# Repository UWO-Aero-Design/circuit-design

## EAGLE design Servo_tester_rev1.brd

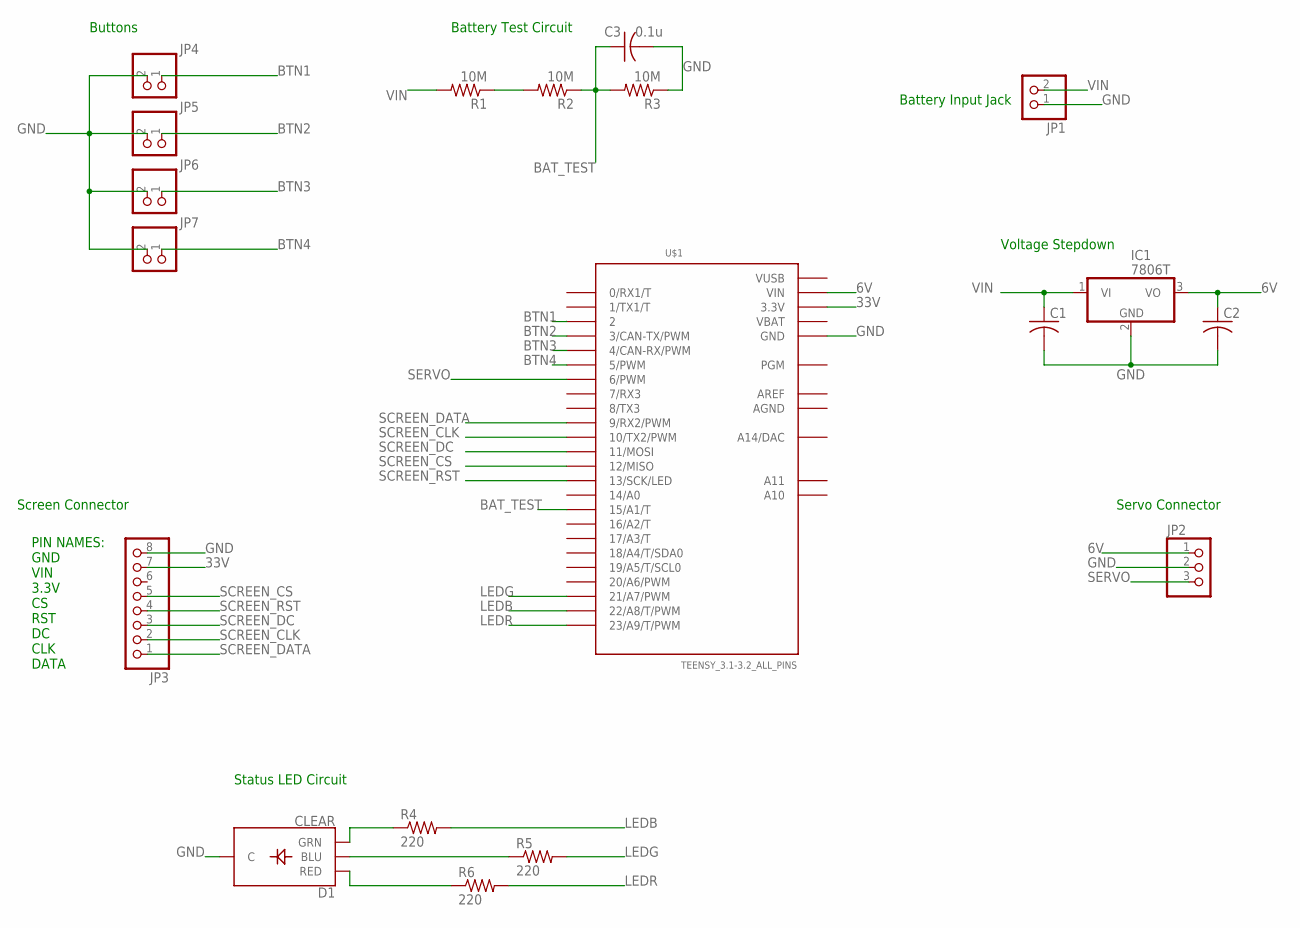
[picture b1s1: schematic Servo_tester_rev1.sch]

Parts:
C1, C2: C-US050-024X044; C050-024X044
C3: 0.1u; C050-024X044
D1: CLEAR; LED-RGB-THRU
IC1: 7806T; TO220H
JP1, JP4, JP5, JP6, JP7: HEADER-1X2ROUND; 1X02_ROUND
JP2: HEADER-1X3ROUND; 1X03_ROUND
JP3: HEADER-1X870MIL; 1X08_ROUND_70
R1, R2, R3: 10M; 0204/5
R4, R5, R6: 220; 0204/5
U$1: TEENSY_3.1-3.2_ALL_PINS; TEENSY_3.0-3.2&LC_ALL_PINS

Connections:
6V: C2.1, IC1.3 (VO), JP2.1, U$1.VIN
33V: JP3.7, U$1.3.3V, U$1.3.3V1 (3.3V)
AGND: U$1.AGND
AREF: U$1.AREF
BAT_TEST: C3.1, R2.1, R3.2, U$1.15/A1 (15/A1/T)
BTN1: JP4.1, U$1.2
BTN2: JP5.1, U$1.3 (3/CAN-TX/PWM)
BTN3: JP6.1, U$1.4 (4/CAN-RX/PWM)
BTN4: JP7.1, U$1.5 (5/PWM)
GND: C1.2, C2.2, C3.2, D1.2 (C), IC1.2 (GND), JP1.1, JP2.2, JP3.8, JP4.2, JP5.2, JP6.2, JP7.2, R3.1, U$1.GND, U$1.GND1 (GND)
LEDB: R4.2, U$1.22/A8 (22/A8/T/PWM)
LEDG: R5.2, U$1.21/A7 (21/A7/PWM)
LEDR: R6.2, U$1.23/A9 (23/A9/T/PWM)
unnamed: D1.1 (RED), R6.1
unnamed: D1.3 (GRN), R4.1
unnamed: D1.4 (BLU), R5.1
unnamed: R1.1, R2.2
SCREEN_CLK: JP3.2, U$1.10 (10/TX2/PWM)
SCREEN_CS: JP3.5, U$1.12 (12/MISO)
SCREEN_DATA: JP3.1, U$1.9 (9/RX2/PWM)
SCREEN_DC: JP3.3, U$1.11 (11/MOSI)
SCREEN_RST: JP3.4, U$1.13 (13/SCK/LED)
SERVO: JP2.3, U$1.6 (6/PWM)
VIN: C1.1, IC1.1 (VI), JP1.2, R1.2, U$1.VBAT
VUSB: U$1.VUSB

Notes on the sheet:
PIN NAMES: GND VIN 3.3V CS RST DC CLK DATA
Battery Input Jack
Battery Test Circuit
Voltage Stepdown
Servo Connector
Status LED Circuit
Screen Connector
Buttons

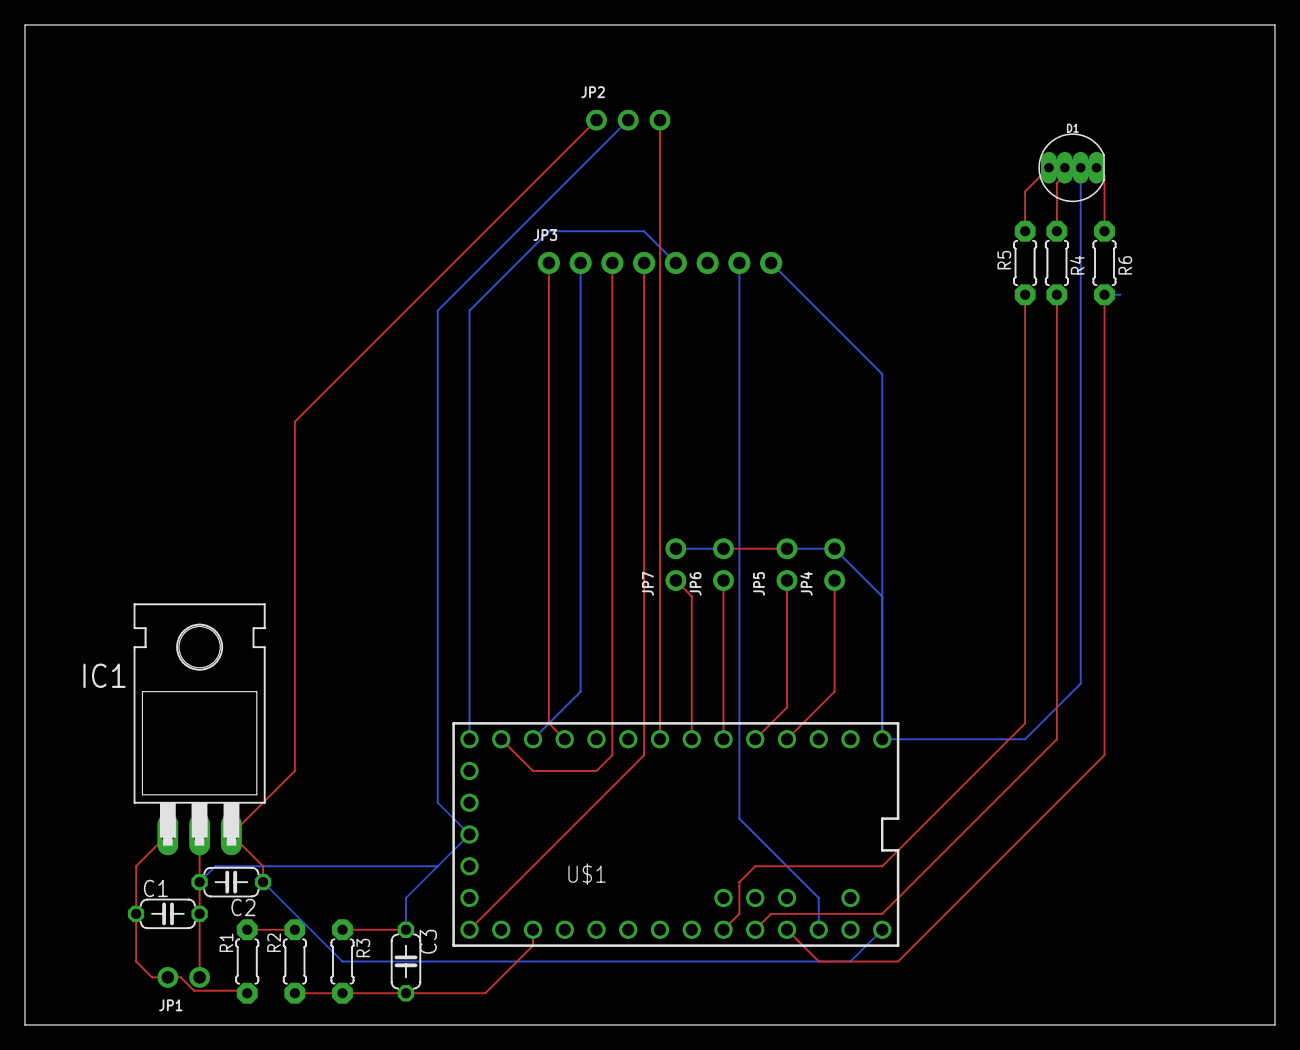
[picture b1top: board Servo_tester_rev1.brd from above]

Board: 2 copper layers, 100.0 x 80.0 mm, 19 parts (0 on the bottom side), 22 nets.

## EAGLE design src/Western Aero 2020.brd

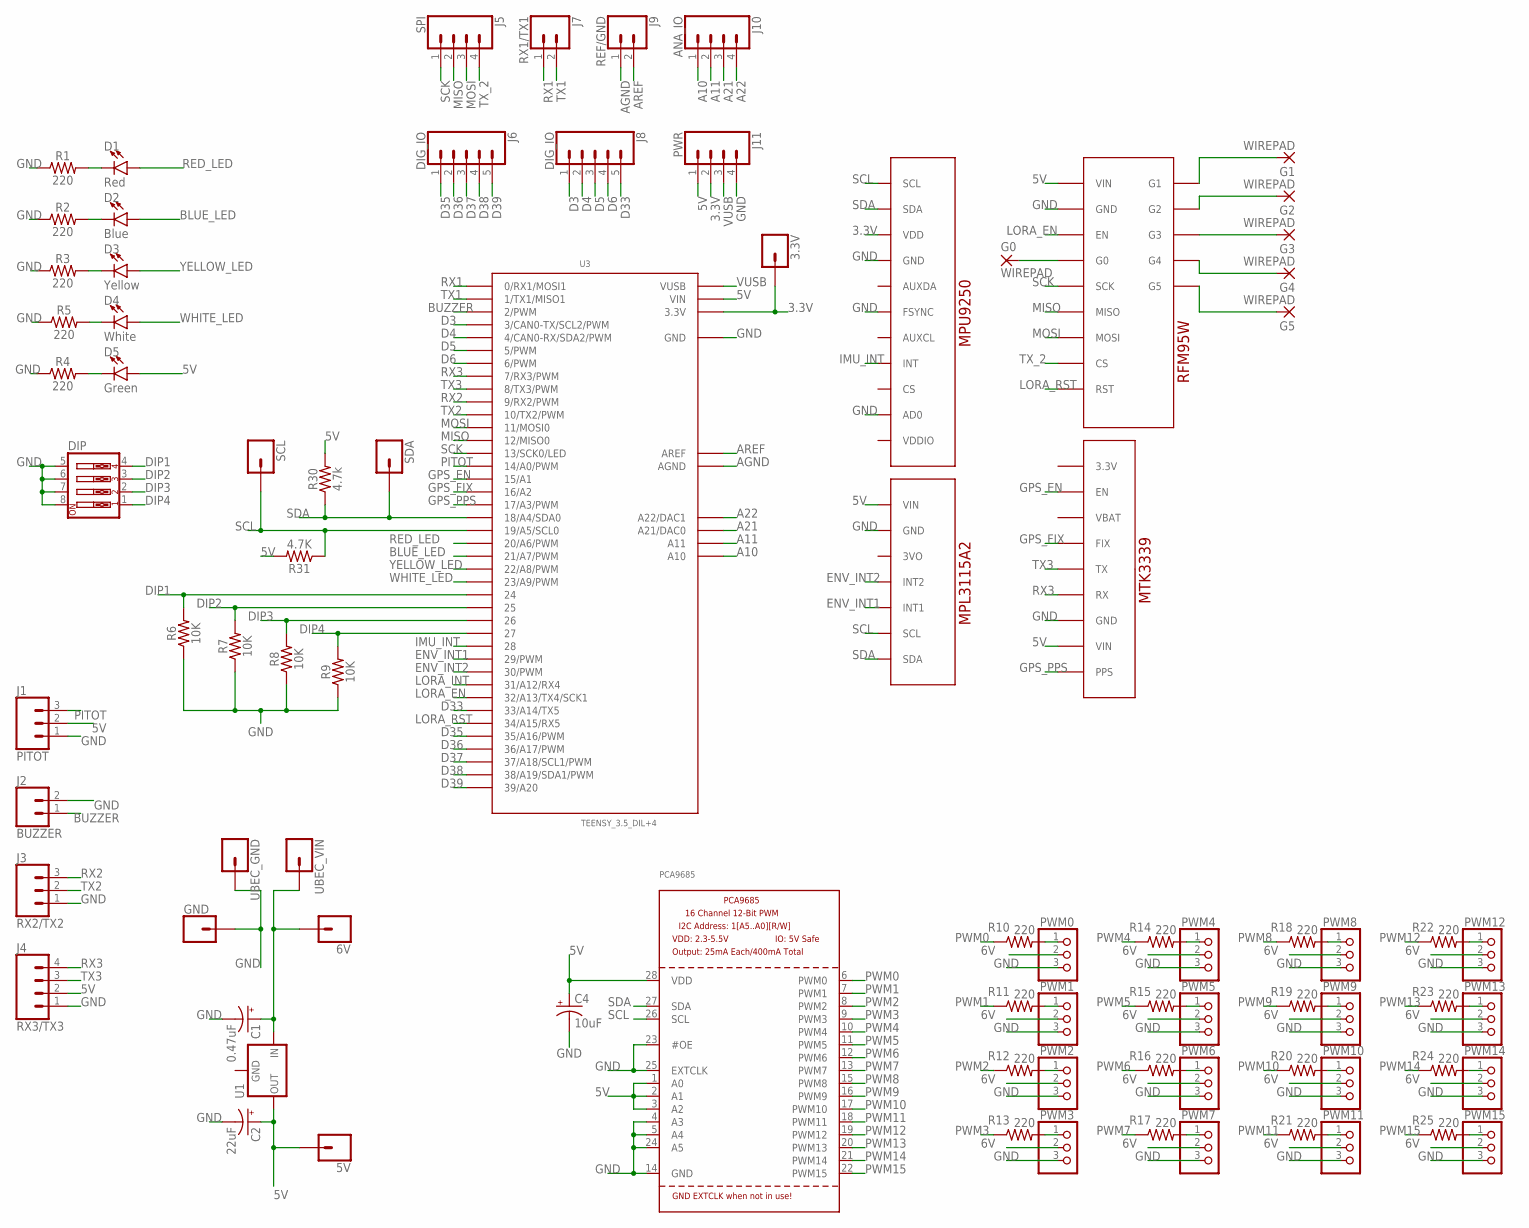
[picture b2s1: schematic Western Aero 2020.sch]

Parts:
3.3V, 5V, 6V: CONN_01; 1X01
C1: 0.47uF; CPOL-RADIAL-2.5MM-5MM
C2: 22uF; CPOL-RADIAL-2.5MM-5MM
C4: 10uF; CPOL-RADIAL-2.5MM-5MM
D1: Red; LED_3MM
D2: Blue; LED_3MM
D3: Yellow; LED_3MM
D4: White; LED_3MM
D5: Green; LED_3MM
DIP: SW_DIP-4; EDG-04
G0, G1, G2, G3, G4, G5: WIREPAD; 2,15/1,0
GND: CONN_01; 1X01
J1: PITOT; 1X03
J2: BUZZER; 1X02
J3: RX2/TX2; 1X03
J4: RX3/TX3; 1X04
J5: SPI; 1X04
J6, J8: DIG_IO; 1X05
J7: RX1/TX1; 1X02
J9: REF/GND; 1X02
J10: ANA_IO; 1X04
J11: PWR; 1X04
JP1: PWM0; 1X03
JP2: PWM1; 1X03
JP3: PWM2; 1X03
JP4: PWM3; 1X03
JP5: PWM4; 1X03
JP6: PWM5; 1X03
JP7: PWM6; 1X03
JP8: PWM7; 1X03
JP9: PWM8; 1X03
JP10: PWM9; 1X03
JP11: PWM10; 1X03
JP12: PWM11; 1X03
JP13: PWM12; 1X03
JP14: PWM13; 1X03
JP15: PWM14; 1X03
JP16: PWM15; 1X03
PCA9685: PCA9685; TSSOP28
R1, R2, R3, R4, R5, R10, R11, R12, R13, R14, R15, R16, R17, R18, R19, R20, R21, R22, R23, R24, R25: 220; AXIAL-0.3
R6, R7, R8, R9: 10K; AXIAL-0.3
R30: 4.7k; AXIAL-0.3
R31: 4.7K; AXIAL-0.3
SCL: CONN_01; 1X01
SDA: CONN_01; 1X01
U1: V_REG_78XXSINK; TO220-IGO
U3: TEENSY_3.5_DIL+4
U5: SPARKFUN_MPU9250_IMU
U6: ADAFRUIT_MPL3115A2_BAROMETER
U8: ADAFRUIT_RFM95W_LORA_RADIO
U9: ADAFRUIT_MTK3339_GPS
UBEC_GND: CONN_01; 1X01
UBEC_VIN: CONN_01; 1X01

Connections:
3.3V: 3.3V.1, J11.2, U3.3.3V, U3.3.3V3 (3.3V), U5.VDD
5V: 5V.1, C2.1 (+), C4.1 (+), D5.A, J1.2, J4.2, J11.1, PCA9685.1 (A0), PCA9685.2 (A1), PCA9685.3 (A2), PCA9685.28 (VDD), R30.P$2 (2), R31.P$2 (2), U1.OUT, U3.VIN, U6.VIN, U8.1 (VIN), U9.VIN
6V: 6V.1, C1.1 (+), JP1.2, JP2.2, JP3.2, JP4.2, JP5.2, JP6.2, JP7.2, JP8.2, JP9.2, JP10.2, JP11.2, JP12.2, JP13.2, JP14.2, JP15.2, JP16.2, U1.IN, UBEC_VIN.1
A10: J10.1, U3.A10
A11: J10.2, U3.A11
A21: J10.3, U3.A21 (A21/DAC0)
A22: J10.4, U3.A22 (A22/DAC1)
AGND: J9.1, U3.AGND
AREF: J9.2, U3.AREF
BLUE_LED: D2.A, U3.21/A7 (21/A7/PWM)
BUZZER: J2.1, U3.2 (2/PWM)
D3: J8.1, U3.3 (3/CAN0-TX/SCL2/PWM)
D4: J8.2, U3.4 (4/CAN0-RX/SDA2/PWM)
D5: J8.3, U3.5 (5/PWM)
D6: J8.4, U3.6 (6/PWM)
D33: J8.5, U3.33/A14 (33/A14/TX5)
D35: J6.1, U3.35/A16 (35/A16/PWM)
D36: J6.2, U3.36/A17 (36/A17/PWM)
D37: J6.3, U3.37/A18 (37/A18/SCL1/PWM)
D38: J6.4, U3.38/A19 (38/A19/SDA1/PWM)
D39: J6.5, U3.39/A20
DIP1: DIP.4, R6.P$2 (2), U3.24
DIP2: DIP.3, R7.P$2 (2), U3.25
DIP3: DIP.2, R8.P$2 (2), U3.26
DIP4: DIP.1, R9.P$2 (2), U3.27
ENV_INT1: U3.29 (29/PWM), U6.INT1
ENV_INT2: U3.30 (30/PWM), U6.INT2
GND: C1.2 (-), C2.2 (-), C4.2 (-), DIP.5, DIP.6, DIP.7, DIP.8, GND.1, J1.1, J2.2, J3.1, J4.1, J11.4, JP1.3, JP2.3, JP3.3, JP4.3, JP5.3, JP6.3, JP7.3, JP8.3, JP9.3, JP10.3, JP11.3, JP12.3, JP13.3, JP14.3, JP15.3, JP16.3, PCA9685.4 (A3), PCA9685.5 (A4), PCA9685.14 (GND), PCA9685.23 (#OE), PCA9685.24 (A5), PCA9685.25 (EXTCLK), R1.P$1 (1), R2.P$1 (1), R3.P$1 (1), R4.P$1 (1), R5.P$1 (1), R6.P$1 (1), R7.P$1 (1), R8.P$1 (1), R9.P$1 (1), U3.GND, U3.GND1 (GND), U5.AD0, U5.FSYNC, U5.GND, U6.GND, U8.2 (GND), U9.GND, UBEC_GND.1
GPS_EN: U3.15/A1, U9.EN
GPS_FIX: U3.16/A2, U9.FIX
GPS_PPS: U3.17/A3 (17/A3/PWM), U9.PPS
IMU_INT: U3.28, U5.INT
LORA_EN: U3.32/A13 (32/A13/TX4/SCK1), U8.3 (EN)
LORA_INT: U3.31/A12 (31/A12/RX4)
LORA_RST: U3.34/A15 (34/A15/RX5), U8.9 (RST)
MISO: J5.2, U3.12 (12/MISO0), U8.6 (MISO)
MOSI: J5.3, U3.11 (11/MOSI0), U8.7 (MOSI)
unnamed: JP1.1, R10.P$2 (2)
unnamed: D1.K (C), R1.P$2 (2)
unnamed: D2.K (C), R2.P$2 (2)
unnamed: D3.K (C), R3.P$2 (2)
unnamed: D4.K (C), R5.P$2 (2)
unnamed: D5.K (C), R4.P$2 (2)
unnamed: G5.1, U8.14 (G5)
unnamed: G1.1, U8.10 (G1)
unnamed: JP2.1, R11.P$2 (2)
unnamed: G2.1, U8.11 (G2)
unnamed: JP3.1, R12.P$2 (2)
unnamed: JP4.1, R13.P$2 (2)
unnamed: JP5.1, R14.P$2 (2)
unnamed: JP6.1, R15.P$2 (2)
unnamed: JP7.1, R16.P$2 (2)
unnamed: JP8.1, R17.P$2 (2)
unnamed: JP9.1, R18.P$2 (2)
unnamed: JP10.1, R19.P$2 (2)
unnamed: JP11.1, R20.P$2 (2)
unnamed: JP12.1, R21.P$2 (2)
unnamed: JP13.1, R22.P$2 (2)
unnamed: JP14.1, R23.P$2 (2)
unnamed: JP15.1, R24.P$2 (2)
unnamed: JP16.1, R25.P$2 (2)
unnamed: G4.1, U8.13 (G4)
unnamed: G3.1, U8.12 (G3)
unnamed: G0.1, U8.4 (G0)
PITOT: J1.3, U3.14/A0 (14/A0/PWM)
PWM0: PCA9685.6 (PWM0), R10.P$1 (1)
PWM1: PCA9685.7 (PWM1), R11.P$1 (1)
PWM2: PCA9685.8 (PWM2), R12.P$1 (1)
PWM3: PCA9685.9 (PWM3), R13.P$1 (1)
PWM4: PCA9685.10 (PWM4), R14.P$1 (1)
PWM5: PCA9685.11 (PWM5), R15.P$1 (1)
PWM6: PCA9685.12 (PWM6), R16.P$1 (1)
PWM7: PCA9685.13 (PWM7), R17.P$1 (1)
PWM8: PCA9685.15 (PWM8), R18.P$1 (1)
PWM9: PCA9685.16 (PWM9), R19.P$1 (1)
PWM10: PCA9685.17 (PWM10), R20.P$1 (1)
PWM11: PCA9685.18 (PWM11), R21.P$1 (1)
PWM12: PCA9685.19 (PWM12), R22.P$1 (1)
PWM13: PCA9685.20 (PWM13), R23.P$1 (1)
PWM14: PCA9685.21 (PWM14), R24.P$1 (1)
PWM15: PCA9685.22 (PWM15), R25.P$1 (1)
RED_LED: D1.A, U3.20/A6 (20/A6/PWM)
RX1: J7.1, U3.0 (0/RX1/MOSI1)
RX2: J3.3, U3.9 (9/RX2/PWM)
RX3: J4.4, U3.7 (7/RX3/PWM), U9.RX
SCK: J5.1, U3.13 (13/SCK0/LED), U8.5 (SCK)
SCL: PCA9685.26 (SCL), R31.P$1 (1), SCL.1, U3.19/A5 (19/A5/SCL0), U5.SCL, U6.SCL
SDA: PCA9685.27 (SDA), R30.P$1 (1), SDA.1, U3.18/A4 (18/A4/SDA0), U5.SDA, U6.SDA
TX1: J7.2, U3.1 (1/TX1/MISO1)
TX2: J3.2, U3.10 (10/TX2/PWM)
TX3: J4.3, U3.8 (8/TX3/PWM), U9.TX
TX_2: J5.4, U8.8 (CS)
VUSB: J11.3, U3.VUSB
WHITE_LED: D4.A, U3.23/A9 (23/A9/PWM)
YELLOW_LED: D3.A, U3.22/A8 (22/A8/PWM)

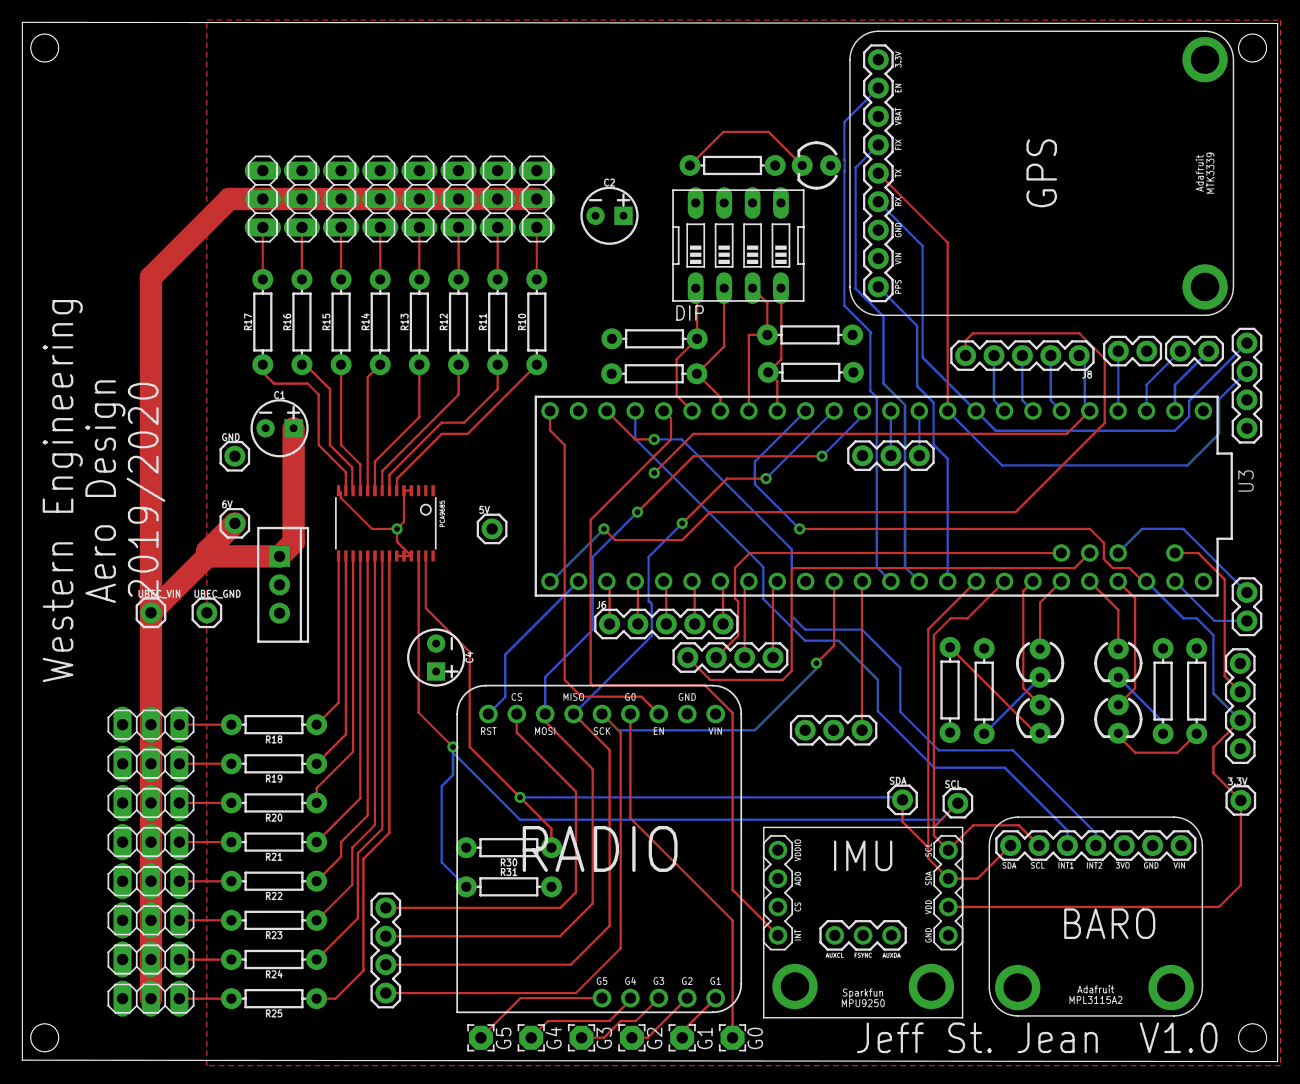
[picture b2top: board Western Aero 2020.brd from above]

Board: 2 copper layers, 112.2 x 92.9 mm, 84 parts (0 on the bottom side), 94 nets.

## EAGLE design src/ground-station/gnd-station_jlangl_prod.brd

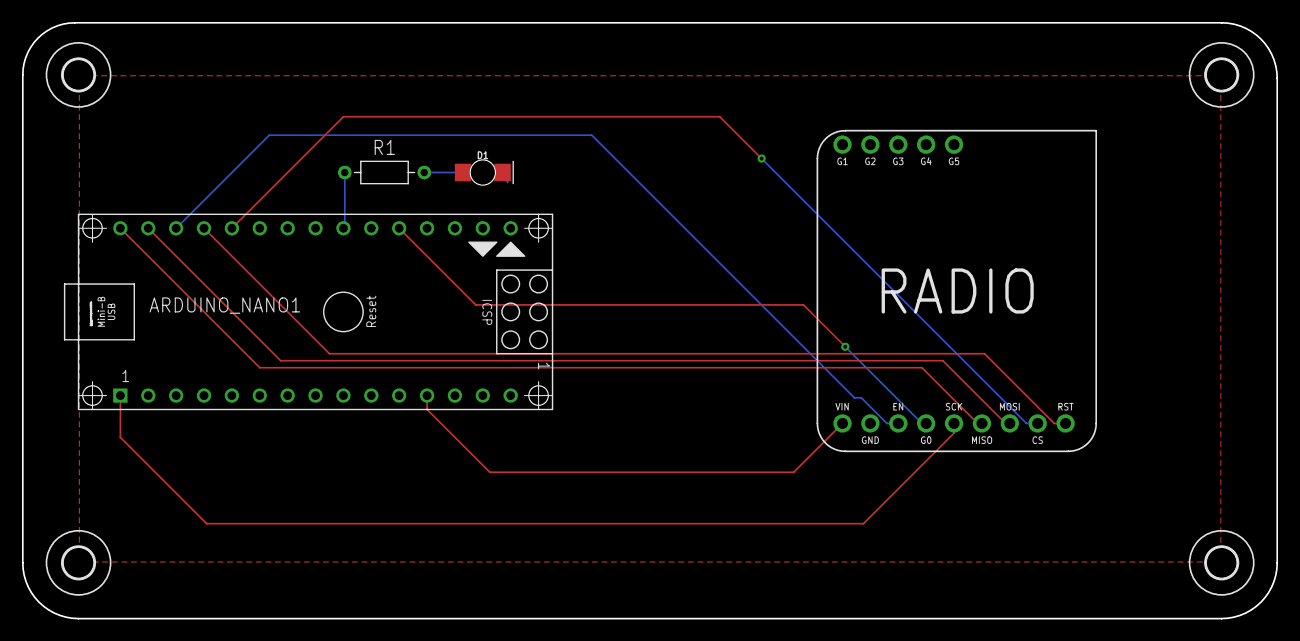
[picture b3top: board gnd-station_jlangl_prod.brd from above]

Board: 2 copper layers, 114.3 x 54.3 mm, 8 parts (0 on the bottom side), 11 nets.

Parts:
ARDUINO_NANO1: ARDUINO_NANO
D1: LED-1206-BOTTOM
H1, H2, H3, H4: MOUNT-HOLE2.8; 2,8
R1: 220; RESAD724W46L381D178B
U1: ADAFRUIT_RFM95W_LORA_RADIO

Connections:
CS: ARDUINO_NANO1.26, U1.8
EN: ARDUINO_NANO1.28, U1.3
G0: ARDUINO_NANO1.20, U1.4
GND: ARDUINO_NANO1.14, ARDUINO_NANO1.19, D1.C, U1.2
LED1: ARDUINO_NANO1.22, R1.1
LORA3.3V: ARDUINO_NANO1.12, U1.1
MISO: ARDUINO_NANO1.30, U1.6
MOSI: ARDUINO_NANO1.29, U1.7
unnamed: D1.A, R1.2
RST: ARDUINO_NANO1.27, U1.9
SCK: ARDUINO_NANO1.1, U1.5

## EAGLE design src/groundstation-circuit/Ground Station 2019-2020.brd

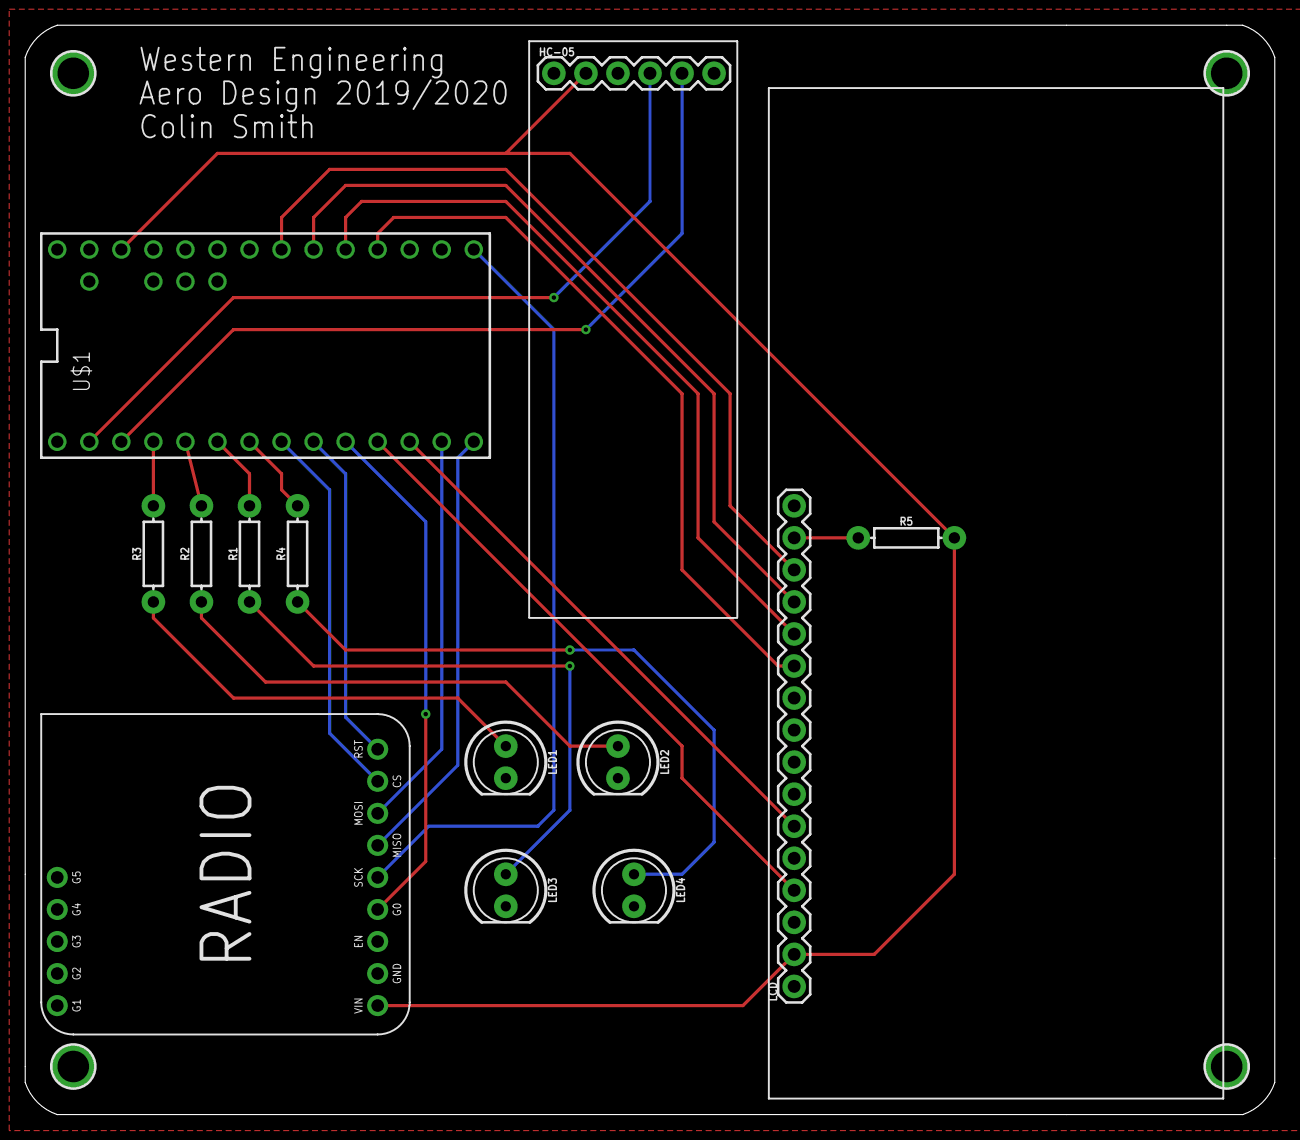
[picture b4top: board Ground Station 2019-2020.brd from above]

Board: 2 copper layers, 99.1 x 86.4 mm, 17 parts (0 on the bottom side), 25 nets.

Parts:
HC-05: 1X06
LCD: 1X16
LED1, LED2, LED3, LED4: LED_5MM
R1, R2, R3, R4: 330; AXIAL-0.3
R5: 220; AXIAL-0.3
U1: ADAFRUIT_RFM95W_LORA_RADIO
U$1: TEENSY_3.1-3.2_DIL+4; TEENSY_3.0-3.2&LC_DIL+4
U$2, U$3, U$4, U$5: MOUNTINGHOLE2.5; MOUNTINGHOLE_2.5_PLATED

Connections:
3.3V: HC-05.2, LCD.2, R5.P$2, U1.1, U$1.3.3V
CS: U1.8, U$1.6
D4: LCD.11, U$1.16/A2
D5: LCD.12, U$1.17/A3
D6: LCD.13, U$1.18/A4
D7: LCD.14, U$1.19/A5
G0: U1.4, U$1.8
GND: HC-05.3, LCD.1, LCD.3, LCD.5, LCD.16, LED1.K, LED2.K, LED3.K, LED4.K, U1.2, U$1.GND
LCD_RX: LCD.4, U$1.9
LCD_TX: LCD.6, U$1.10
LED1: R3.P$2, U$1.2
LED2: R2.P$2, U$1.3
LED3: R1.P$2, U$1.4
LED4: R4.P$2, U$1.5
MISO: U1.6, U$1.12
MOSI: U1.7, U$1.11
unnamed: LED3.A, R1.P$1
unnamed: LED2.A, R2.P$1
unnamed: LED1.A, R3.P$1
unnamed: LCD.15, R5.P$1
unnamed: LED4.A, R4.P$1
RST: U1.9, U$1.7
RX1: HC-05.4, U$1.0
SCK: U1.5, U$1.13
TX1: HC-05.5, U$1.1

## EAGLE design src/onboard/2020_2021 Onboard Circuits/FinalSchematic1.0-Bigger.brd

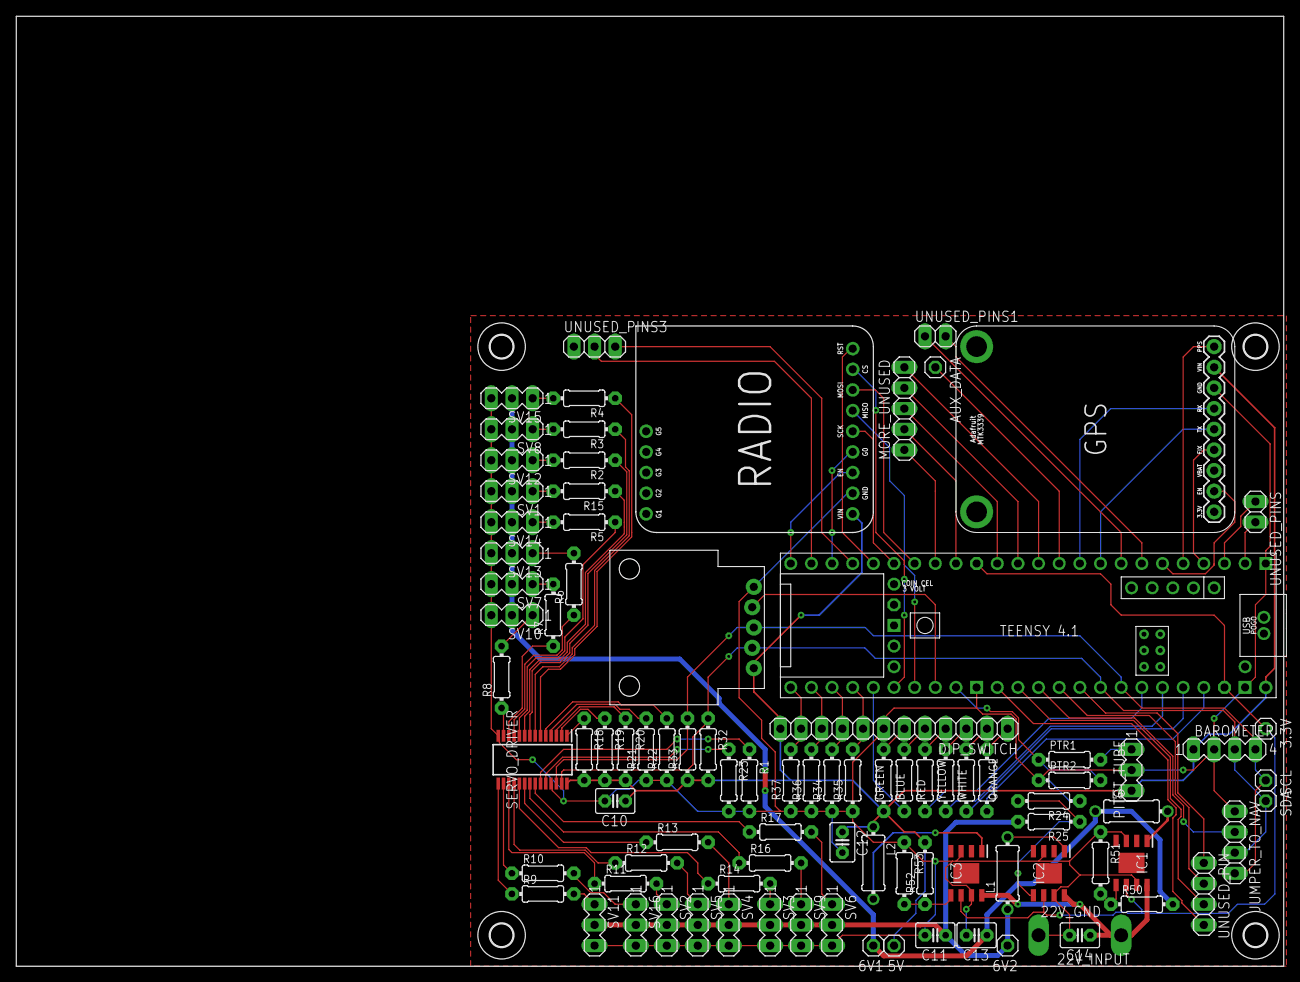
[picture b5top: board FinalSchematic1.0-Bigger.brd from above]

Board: 2 copper layers, 155.9 x 116.8 mm, 97 parts (0 on the bottom side), 100 nets.

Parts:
3.3V, 5V, 6V1, 6V2: 1X01
22V_GND, 22V_INPUT: TPPAD1-17Y; P1-17Y
AUX_DATA: 1X01
BAROMETER: MA04-1
BLUE: 80; 0204/7
C10, C14: 10uF; C2.5-3
C11, C12, C13: 470uF; C2.5-3
DIP_SWITCH: 1X12
GPSMTK3339: ADAFRUIT_MTK3339_GPS
GREEN: 150; 0204/7
IC1, IC2, IC3: A5975D; SOIC127P600X170-9N
JUMPER_TO_NAV: 1X04
L1, L2, L6: 27uH; TFI0307
MORE_UNUSED: 1X05
ORANGE: 150; 0204/7
PITOT_TUBE: MA03-1
PTR1: 2.2K; 0204/7
PTR2: 4.3K; 0204/7
R1, R23: 10k; 0204/7
R2, R3, R4, R5, R6, R7, R8, R9, R10, R11, R12, R13, R14, R15, R16, R17: 220; 0204/7
R18, R19, R20, R21, R22: 10K; 0204/7
R24, R51: 1.5k; 0204/7
R25, R50: 5.6k; 0204/7
R32, R33: 4.7k; 0204/7
R34, R35, R36, R37: 2.2k; 0204/7
R52: 1k; 0204/7
R53: 3k; 0204/7
RADIO: ADAFRUIT_RFM95W_LORA_RADIO
RED: 150; 0204/7
SCL: 1X01
SDA: 1X01
SERVO_DRIVER: PCA9685PW,112; SOP65P640X110-28N
SV1, SV2, SV3, SV4, SV5, SV6, SV7, SV8, SV9, SV10, SV11, SV12, SV13, SV14, SV15, SV16: MA03-1
TEENSY4.1: TEENSY41
U$1, U$3, U$4, U$5: 2,8
U$2: ICM20948BREAKOUTDEVICE; ICM20948BREAKOUT
UNUSED_PIN: 1X04
UNUSED_PINS, UNUSED_PINS1: 1X02
UNUSED_PINS3: 1X03
WHITE: 90; 0204/7
YELLOW: 150; 0204/7

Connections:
3.3V: 3.3V.1, IC1.6, IC2.6, IC3.6, TEENSY4.1.3V3-1, TEENSY4.1.3V3-3
5V: 5V.1, BAROMETER.1, C10.1, C12.1, DIP_SWITCH.12, GPSMTK3339.VIN, GREEN.1, L2.1, PITOT_TUBE.3, R18.2, R19.2, R20.2, R32.2, R33.1, R52.2, RADIO.1, SERVO_DRIVER.28, TEENSY4.1.VIN, U$2.2-6V
AUX_DATA: AUX_DATA.1, TEENSY4.1.9-OUT1C
B_LED: BLUE.1, TEENSY4.1.37-PWM
DIP1: DIP_SWITCH.11, R37.2, TEENSY4.1.33-MCLK2
DIP2: DIP_SWITCH.10, R36.2, TEENSY4.1.34-RX8
DIP3: DIP_SWITCH.9, R34.2, TEENSY4.1.35-TX8
DIP4: DIP_SWITCH.8, R35.2, TEENSY4.1.36-PWM
GND: 22V_GND.TP, BAROMETER.2, C10.2, C11.2, C12.2, C13.2, C14.2, DIP_SWITCH.7, GPSMTK3339.GND, IC1.3, IC1.7, IC2.3, IC2.7, IC3.3, IC3.7, JUMPER_TO_NAV.1, PITOT_TUBE.2, PTR2.1, R1.2, R21.1, R22.1, R23.2, R24.1, R34.1, R35.1, R36.1, R37.1, R51.1, R53.1, RADIO.2, SERVO_DRIVER.14, SERVO_DRIVER.25, SV1.3, SV2.3, SV3.3, SV4.3, SV5.3, SV6.3, SV7.3, SV8.3, SV9.3, SV10.3, SV11.3, SV12.3, SV13.3, SV14.3, SV15.3, SV16.3, TEENSY4.1.GND1, TEENSY4.1.GND3, TEENSY4.1.GND6, U$2.GND
GPS_EN: GPSMTK3339.EN, TEENSY4.1.4-BCLK2
GPS_FIX: GPSMTK3339.FIX, TEENSY4.1.2-OUT2
GPS_PPS: GPSMTK3339.PPS, TEENSY4.1.3-LRCLK2
IMU_INT: TEENSY4.1.40-A16/CS1, U$2.INT
MISO1: RADIO.6, TEENSY4.1.39-A15/CS/OUT1A
MOSI1: RADIO.7, TEENSY4.1.26-A12/MOSI1
unnamed: DIP_SWITCH.4, RED.2
unnamed: R14.2, SV3.1
unnamed: BLUE.2, DIP_SWITCH.5
unnamed: PITOT_TUBE.1, PTR1.2
unnamed: 22V_INPUT.TP, C14.1, IC1.8, IC2.8, IC3.8
unnamed: IC3.1, L2.2
unnamed: DIP_SWITCH.6, GREEN.2
unnamed: IC1.1, L6.2
unnamed: IC1.5, R50.1, R51.2
unnamed: DIP_SWITCH.3, YELLOW.2
unnamed: DIP_SWITCH.2, WHITE.2
unnamed: IC2.1, L1.2
unnamed: R23.1, SERVO_DRIVER.24
unnamed: R1.1, SERVO_DRIVER.23
unnamed: DIP_SWITCH.1, ORANGE.2
unnamed: IC3.5, R52.1, R53.2
unnamed: IC2.5, R24.2, R25.1
unnamed: R10.2, SV16.1
unnamed: R22.2, SERVO_DRIVER.5
unnamed: R21.2, SERVO_DRIVER.4
unnamed: R20.1, SERVO_DRIVER.3
unnamed: R19.1, SERVO_DRIVER.2
unnamed: R18.1, SERVO_DRIVER.1
unnamed: R6.2, SV13.1
unnamed: R4.2, SV15.1
unnamed: R3.2, SV8.1
unnamed: R7.2, SV7.1
unnamed: R11.2, SV2.1
unnamed: R15.2, SV1.1
unnamed: R2.2, SV12.1
unnamed: R5.2, SV14.1
unnamed: R9.2, SV11.1
unnamed: R8.2, SV10.1
unnamed: R12.2, SV5.1
unnamed: R16.2, SV9.1
unnamed: R17.2, SV6.1
unnamed: R13.2, SV4.1
OUTPUT_BUCK1: 6V1.1, C13.1, L6.1, R50.2, SV1.2, SV7.2, SV8.2, SV10.2, SV12.2, SV13.2, SV14.2, SV15.2
OUTPUT_BUCK2: 6V2.1, C11.1, L1.1, R25.2, SV2.2, SV3.2, SV4.2, SV5.2, SV6.2, SV9.2, SV11.2, SV16.2
O_LED: ORANGE.1, TEENSY4.1.23-A9/CRX1/MCLK1
PIN0: TEENSY4.1.0-RX1/CS1/CRX2, UNUSED_PINS.2
PIN1: TEENSY4.1.1-TX1/MISO1/CTX2, UNUSED_PINS.1
PIN5: TEENSY4.1.5-IN2, UNUSED_PINS1.2
PIN6: TEENSY4.1.6-OUT1D, UNUSED_PINS1.1
PIN10: MORE_UNUSED.5, TEENSY4.1.10-CS\MQSR
PIN11: MORE_UNUSED.4, TEENSY4.1.11-MOSI/CTX1
PIN12: MORE_UNUSED.3, TEENSY4.1.12-MISO/MQSL
PIN13: TEENSY4.1.13-SCK/LED, UNUSED_PIN.4
PIN14: TEENSY4.1.14-A0/TX3/SPDIF_OUT, UNUSED_PIN.3
PIN16: TEENSY4.1.16-A2/RX4/SCL1, UNUSED_PIN.2
PIN17: TEENSY4.1.17-A3/TX4/SDA1, UNUSED_PIN.1
PIN24: MORE_UNUSED.2, TEENSY4.1.24-A10/TX6/SCL2
PIN25: MORE_UNUSED.1, TEENSY4.1.25-A11/RX6/SDA2
PIN29: TEENSY4.1.29-TX7, UNUSED_PINS3.3
PIN31: TEENSY4.1.31-CTX3, UNUSED_PINS3.2
PT_ANLGPIN: PTR1.1, PTR2.2, TEENSY4.1.41-A17/MISO1
PWM0: R4.1, SERVO_DRIVER.6
PWM1: R3.1, SERVO_DRIVER.7
PWM2: R2.1, SERVO_DRIVER.8
PWM3: R15.1, SERVO_DRIVER.9
PWM4: R5.1, SERVO_DRIVER.10
PWM5: R6.1, SERVO_DRIVER.11
PWM6: R7.1, SERVO_DRIVER.12
PWM7: R8.1, SERVO_DRIVER.13
PWM8: R9.1, SERVO_DRIVER.15
PWM9: R10.1, SERVO_DRIVER.16
PWM10: R11.1, SERVO_DRIVER.17
PWM11: R12.1, SERVO_DRIVER.18
PWM12: R14.1, SERVO_DRIVER.19
PWM13: R13.1, SERVO_DRIVER.20
PWM14: R16.1, SERVO_DRIVER.21
PWM15: R17.1, SERVO_DRIVER.22
RADIO_CS: RADIO.8, TEENSY4.1.38-A14/CS/IN1
RADIO_EN: RADIO.3, TEENSY4.1.32-OUT1B
RADIO_INT: RADIO.4, TEENSY4.1.30-CRX3
RADIO_RST: RADIO.9, TEENSY4.1.28-RX7
RX2: GPSMTK3339.TX, TEENSY4.1.7-RX2/OUT1A
R_LED: RED.1, TEENSY4.1.20-A6/TX5/LRCLK1
SCK1: RADIO.5, TEENSY4.1.27-A13/SCK1
SCL: BAROMETER.4, JUMPER_TO_NAV.4, R33.2, SCL.1, SERVO_DRIVER.26, TEENSY4.1.19-A5/SCL0, U$2.SCL
SDA: BAROMETER.3, JUMPER_TO_NAV.3, R32.1, SDA.1, SERVO_DRIVER.27, TEENSY4.1.18-A4/SDA0, U$2.SDA
SELECT_PIN: JUMPER_TO_NAV.2, TEENSY4.1.15-A1/RX3/SPDIF_IN
TX2: GPSMTK3339.RX, TEENSY4.1.8-TX2/IN1
W_LED: TEENSY4.1.22-A8/CTX1, WHITE.1
Y_LED: TEENSY4.1.21-A7/RX5/BCLK1, YELLOW.1

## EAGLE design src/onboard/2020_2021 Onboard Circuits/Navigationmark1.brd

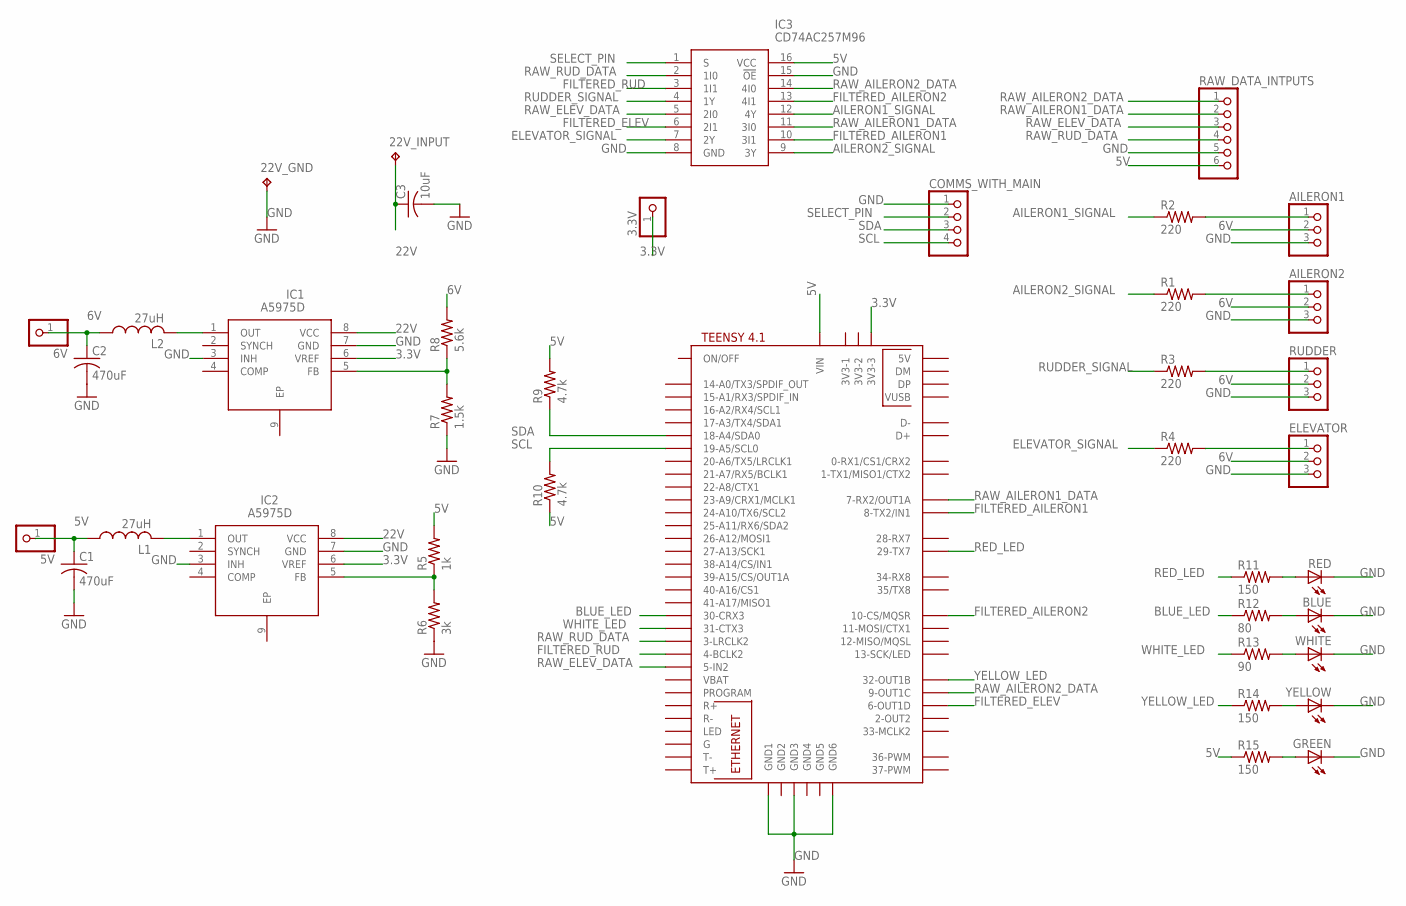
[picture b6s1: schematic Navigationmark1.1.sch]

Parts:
3.3V, 5V, 6V: PINHD-1X1; 1X01
22V_GND, 22V_INPUT: TPPAD1-17Y; P1-17Y
AILERON1, AILERON2: PINHD-1X3; 1X03
BLUE: LED3MM
C1, C2: 470uF; C075-032X103
C3: 10uF; C075-032X103
COMMS_WITH_MAIN: PINHD-1X4; 1X04
ELEVATOR: PINHD-1X3; 1X03
GREEN: LED3MM
IC1, IC2: A5975D; SOIC127P600X170-9N
IC3: CD74AC257M96; SOIC127P600X175-16N
L1, L2: 27uH; 0207/10
R1, R2, R3, R4: 220; 0204/7
R5: 1k; 0204/7
R6: 3k; 0204/7
R7: 1.5k; 0204/7
R8: 5.6k; 0204/7
R9, R10: 4.7k; 0204/7
R11, R14, R15: 150; 0204/7
R12: 80; 0204/7
R13: 90; 0204/7
RAW_DATA_INTPUTS: PINHD-1X6; 1X06
RED: LED3MM
RUDDER: PINHD-1X3; 1X03
U$1: TEENSY41
WHITE: LED3MM
YELLOW: LED3MM

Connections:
3.3V: 3.3V.1, IC1.6 (VREF), IC2.6 (VREF), U$1.3V3-3
5V: 5V.1, C1.1, IC3.16 (VCC), L1.1, R5.2, R9.2, R10.1, R15.1, RAW_DATA_INTPUTS.6, U$1.VIN
6V: 6V.1, AILERON1.2, AILERON2.2, C2.1, ELEVATOR.2, L2.1, R8.2, RUDDER.2
22V: 22V_INPUT.TP, C3.1, IC1.8 (VCC), IC2.8 (VCC)
AILERON1_SIGNAL: IC3.12 (4Y), R2.1
AILERON2_SIGNAL: IC3.9 (3Y), R1.1
BLUE_LED: R12.1, U$1.30-CRX3
ELEVATOR_SIGNAL: IC3.7 (2Y), R4.1
FILTERED_AILERON1: IC3.10 (3I1), U$1.8-TX2/IN1
FILTERED_AILERON2: IC3.13 (4I1), U$1.10-CS\MQSR (10-CS/MQSR)
FILTERED_ELEV: IC3.6 (2I1), U$1.6-OUT1D
FILTERED_RUD: IC3.3 (1I1), U$1.4-BCLK2
GND: 22V_GND.TP, AILERON1.3, AILERON2.3, BLUE.K (C), C1.2, C2.2, C3.2, COMMS_WITH_MAIN.1, ELEVATOR.3, GREEN.K (C), IC1.3 (INH), IC1.7 (GND), IC2.3 (INH), IC2.7 (GND), IC3.8 (GND), IC3.15 (!OE), R6.1, R7.1, RAW_DATA_INTPUTS.5, RED.K (C), RUDDER.3, U$1.GND1, U$1.GND3, U$1.GND6, WHITE.K (C), YELLOW.K (C); also elsewhere on the board
unnamed: AILERON1.1, R2.2
unnamed: GREEN.A, R15.2
unnamed: AILERON2.1, R1.2
unnamed: R3.2, RUDDER.1
unnamed: IC1.1 (OUT), L2.2
unnamed: R11.2, RED.A
unnamed: ELEVATOR.1, R4.2
unnamed: IC2.1 (OUT), L1.2
unnamed: IC2.5 (FB), R5.1, R6.2
unnamed: IC1.5 (FB), R7.2, R8.1
unnamed: BLUE.A, R12.2
unnamed: R13.2, WHITE.A
unnamed: R14.2, YELLOW.A
RAW_AILERON1_DATA: IC3.11 (3I0), RAW_DATA_INTPUTS.2, U$1.7-RX2/OUT1A
RAW_AILERON2_DATA: IC3.14 (4I0), RAW_DATA_INTPUTS.1, U$1.9-OUT1C
RAW_ELEV_DATA: IC3.5 (2I0), RAW_DATA_INTPUTS.3, U$1.5-IN2
RAW_RUD_DATA: IC3.2 (1I0), RAW_DATA_INTPUTS.4, U$1.3-LRCLK2
RED_LED: R11.1, U$1.29-TX7
RUDDER_SIGNAL: IC3.4 (1Y), R3.1
SCL: COMMS_WITH_MAIN.4, R10.2, U$1.19-A5/SCL0; also elsewhere on the board
SDA: COMMS_WITH_MAIN.3, R9.1, U$1.18-A4/SDA0; also elsewhere on the board
SELECT_PIN: COMMS_WITH_MAIN.2, IC3.1 (S); also elsewhere on the board
WHITE_LED: R13.1, U$1.31-CTX3
YELLOW_LED: R14.1, U$1.32-OUT1B

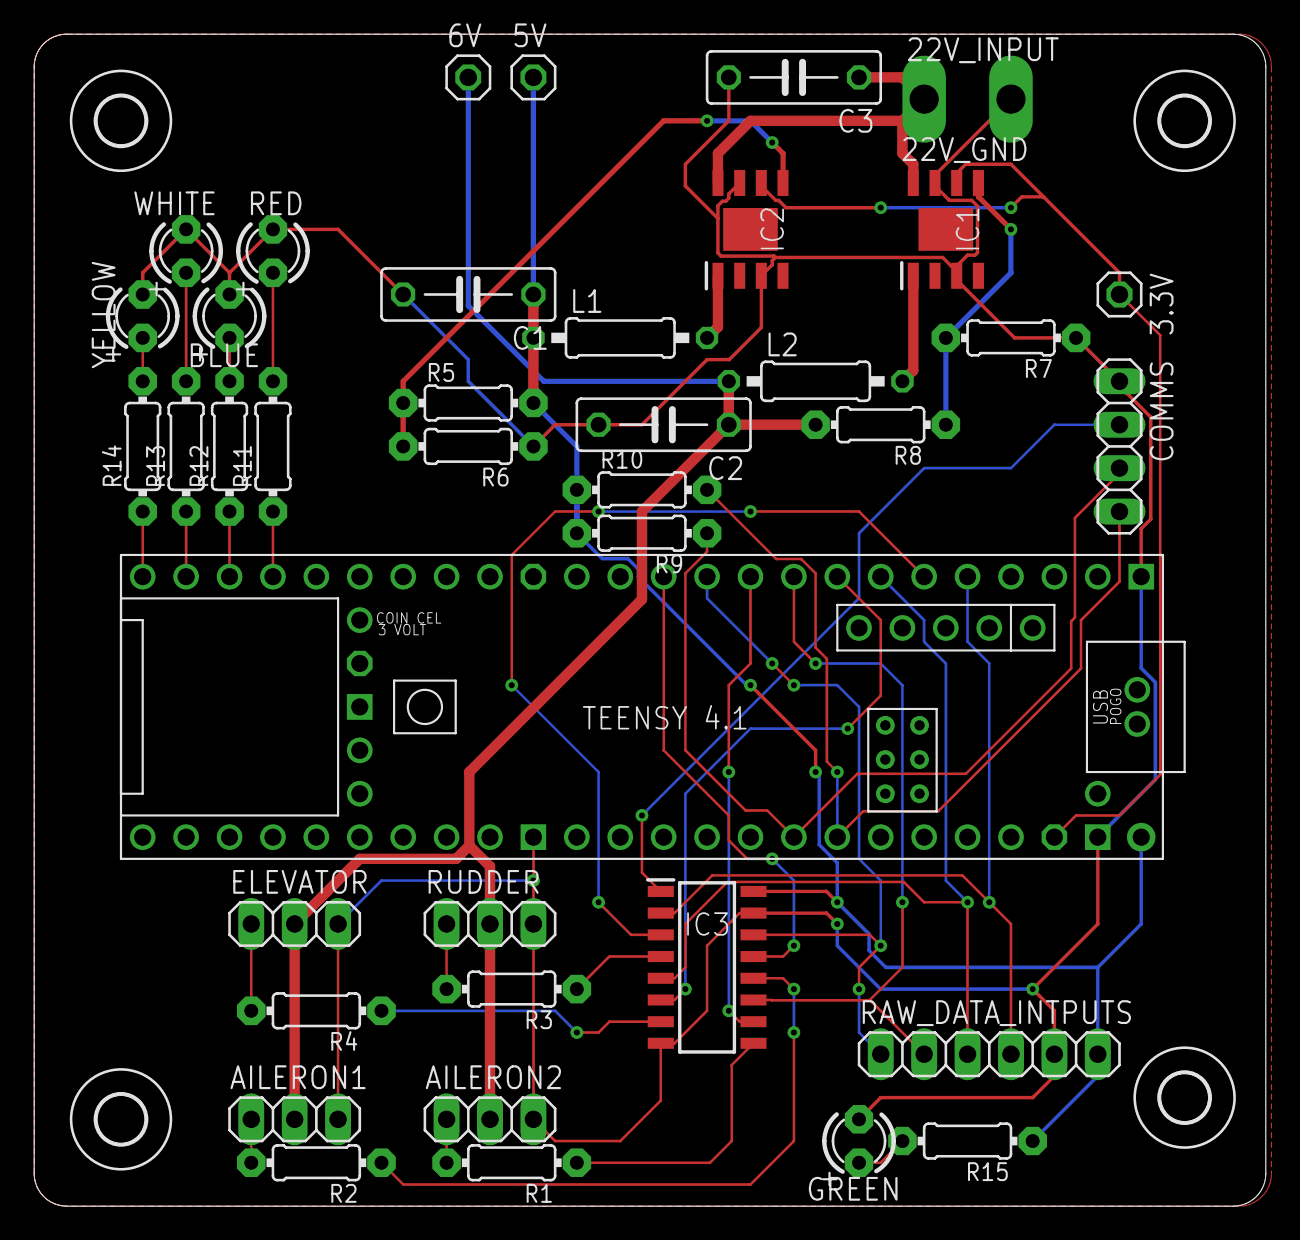
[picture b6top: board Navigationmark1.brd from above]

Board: 2 copper layers, 72.1 x 68.6 mm, 44 parts (0 on the bottom side), 37 nets.

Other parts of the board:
COMMS: 1X04
U$2, U$3, U$4, U$5: 2,8

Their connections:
GND: COMMS.1; also elsewhere on the board
SCL: COMMS.4; also elsewhere on the board
SDA: COMMS.3; also elsewhere on the board
SELECT_PIN: COMMS.2; also elsewhere on the board

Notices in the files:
parts and their libraries:
SparkFun-LED: Licensing: Creative Commons ShareAlike 4.0 International - https://creativecommons.org/licenses/by-sa/4.0
microbuilder: This work is placed in the public domain, and may be freely used for commercial and non-commercial work with the following conditions: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
